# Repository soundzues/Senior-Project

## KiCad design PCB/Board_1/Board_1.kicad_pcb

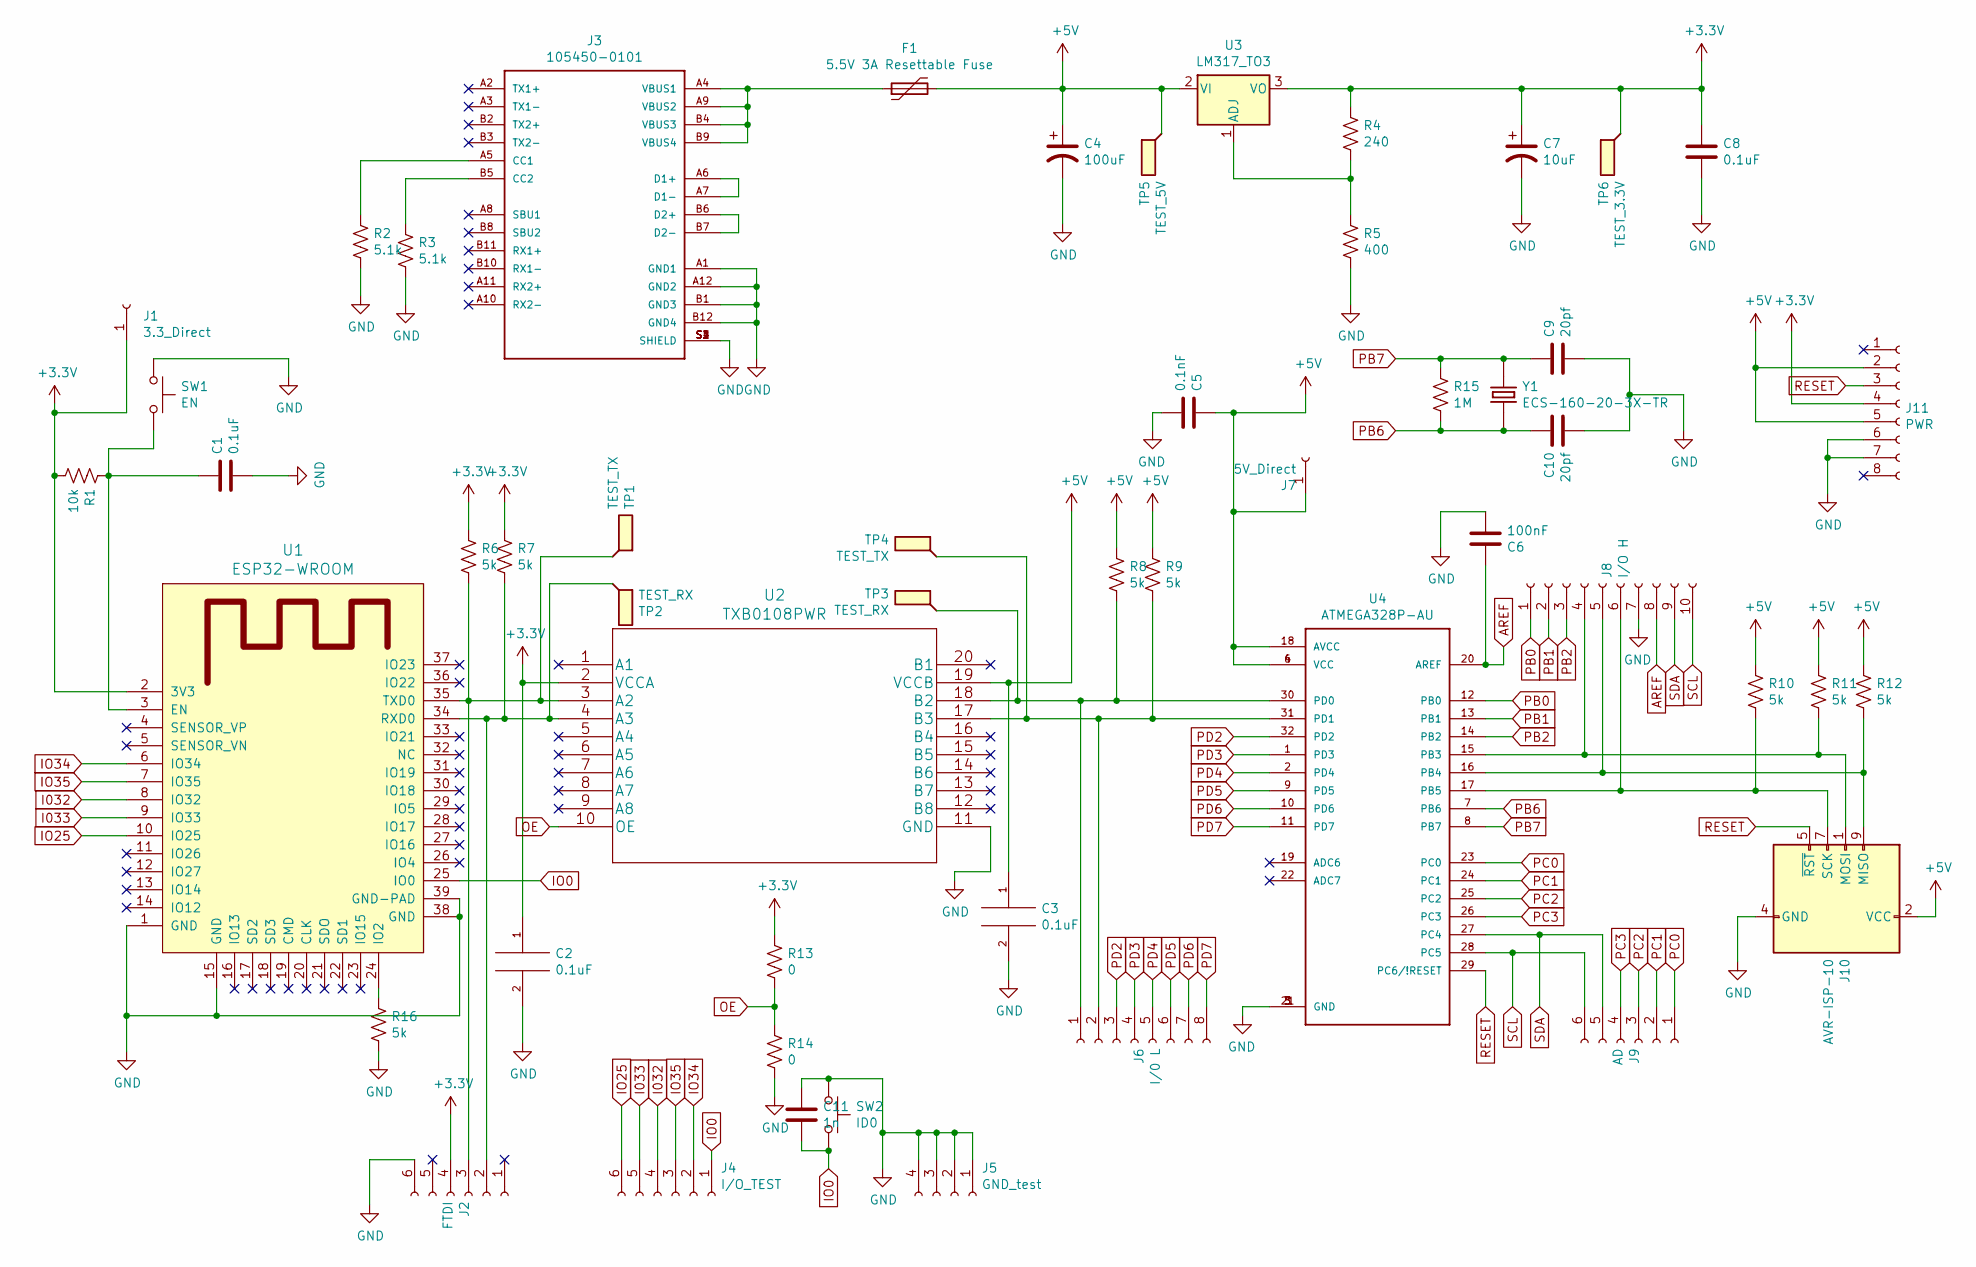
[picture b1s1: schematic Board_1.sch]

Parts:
C1, C2, C3, C8: 0.1uF; C_0603_1608Metric
C4: 100uF; C_0603_1608Metric
C5: 0.1nF; C_0603_1608Metric
C6: 100nF; C_0603_1608Metric
C7: 10uF; C_0603_1608Metric
C9, C10: 20pf; C_0603_1608Metric
C11: 1n; C_0603_1608Metric
F1: 5.5V 3A Resettable Fuse; Fuse_0805_2012Metric
J1: 3.3_Direct; PinHeader_1x01_P2.54mm_Vertical
J2: FTDI; PinHeader_1x06_P2.54mm_Vertical
J3: 105450-0101; MOLEX_105450-0101
J4: I/O_TEST; PinHeader_1x06_P2.54mm_Vertical
J5: GND_test; PinHeader_1x04_P2.54mm_Vertical
J6: I/0 L; PinHeader_1x08_P2.54mm_Vertical
J7: 5V_Direct; PinHeader_1x01_P2.54mm_Vertical
J8: I/O H; PinHeader_1x10_P2.54mm_Vertical
J9: AD; PinHeader_1x06_P2.54mm_Vertical
J10: AVR-ISP-10; PinHeader_2x05_P2.54mm_Vertical
J11: PWR; PinHeader_1x08_P2.54mm_Vertical
R1: 10k; R_0603_1608Metric
R2, R3: 5.1k; R_0603_1608Metric
R4: 240; R_0603_1608Metric
R5: 400; R_0603_1608Metric
R6, R7, R8, R9, R10, R11, R12, R16: 5k; R_0603_1608Metric
R13, R14: 0; R_0603_1608Metric
R15: 1M; R_0603_1608Metric
SW1: EN; SW_PUSH_6mm
SW2: ID0; SW_PUSH_6mm
TP1, TP4: TEST_TX; PinHeader_1x01_P2.54mm_Vertical
TP2, TP3: TEST_RX; PinHeader_1x01_P2.54mm_Vertical
TP5: TEST_5V; PinHeader_1x01_P2.54mm_Vertical
TP6: TEST_3.3V; PinHeader_1x01_P2.54mm_Vertical
U1: ESP32-WROOM
U2: TXB0108PWR
U3: LM317_TO3; TO-220-3_Vertical
U4: ATMEGA328P-AU; QFP80P900X900X120-32N
Y1: ECS-160-20-3X-TR; XTAL_ECS-160-20-3X-TR

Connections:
+3V3: C2.1, C7.1, C8.1, J1.1, J2.4, J11.4, R1.2, R4.1, R6.1, R7.1, R13.1, TP6.1, U1.2 (3V3), U2.2 (VCCA), U3.3 (VO)
+5V: C3.1, C4.1, C5.1, F1.2, J7.1, J10.2 (VCC), J11.2, J11.5, R8.1, R9.1, R10.1, R11.1, R12.1, TP5.1, U2.19 (VCCB), U3.2 (VI), U4.4 (VCC), U4.6 (VCC), U4.18 (AVCC)
AREF: C6.1, J8.8, U4.20 (AREF)
GND: C1.2, C2.2, C3.2, C4.2, C5.2, C6.2, C7.2, C8.2, C9.2, C10.2, C11.1, J2.6, J3.A1 (GND1), J3.A12 (GND2), J3.B1 (GND3), J3.B12 (GND4), J3.S1 (SHIELD), J3.S2 (SHIELD), J3.S3 (SHIELD), J3.S4 (SHIELD), J5.1, J5.2, J5.3, J5.4, J8.7, J10.4 (GND), J10.6 (GND), J10.8 (GND), J10.10 (GND), J11.6, J11.7, R2.2, R3.2, R5.2, R14.2, R16.2, SW1.1, SW2.1, U1.1 (GND), U1.15 (GND), U1.38 (GND), U1.39 (GND-PAD), U2.11 (GND), U4.3 (GND), U4.5 (GND), U4.21 (GND)
I032: J4.4, U1.8 (IO32)
I033: J4.5, U1.9 (IO33)
IO0: C11.2, J4.1, SW2.2, U1.25 (IO0)
IO25: J4.6, U1.10 (IO25)
IO34: J4.2, U1.6 (IO34)
IO35: J4.3, U1.7 (IO35)
unnamed: C1.1, R1.1, SW1.2, U1.3 (EN)
unnamed: F1.1, J3.A4 (VBUS1), J3.A9 (VBUS2), J3.B4 (VBUS3), J3.B9 (VBUS4)
unnamed: J2.2, R7.2, TP2.1, U1.34 (RXD0), U2.4 (A3)
unnamed: J2.3, R6.2, TP1.1, U1.35 (TXD0), U2.3 (A2)
unnamed: J3.A5 (CC1), R2.1
unnamed: J3.A6 (D1+), J3.A7 (D1-)
unnamed: J3.B5 (CC2), R3.1
unnamed: J3.B6 (D2+), J3.B7 (D2-)
unnamed: J6.1, R8.2, TP3.1, U2.18 (B2), U4.30 (PD0)
unnamed: J6.2, R9.2, TP4.1, U2.17 (B3), U4.31 (PD1)
unnamed: J8.4, J10.1 (MOSI), R11.2, U4.15 (PB3)
unnamed: J8.6, J10.7 (SCK), R10.2, U4.17 (PB5)
unnamed: J8.5, J10.9 (MISO), R12.2, U4.16 (PB4)
unnamed: R4.2, R5.1, U3.1 (ADJ)
unnamed: R16.1, U1.24 (IO2)
OE: R13.2, R14.1, U2.10 (OE)
PB0: J8.1, U4.12 (PB0)
PB1: J8.2, U4.13 (PB1)
PB2: J8.3, U4.14 (PB2)
PB6: C10.1, R15.2, U4.7 (PB6), Y1.2
PB7: C9.1, R15.1, U4.8 (PB7), Y1.1
PC0: J9.1, U4.23 (PC0)
PC1: J9.2, U4.24 (PC1)
PC2: J9.3, U4.25 (PC2)
PC3: J9.4, U4.26 (PC3)
PD2: J6.3, U4.32 (PD2)
PD3: J6.4, U4.1 (PD3)
PD4: J6.5, U4.2 (PD4)
PD5: J6.6, U4.9 (PD5)
PD6: J6.7, U4.10 (PD6)
PD7: J6.8, U4.11 (PD7)
RESET: J10.5 (~RST), J11.3, U4.29 (PC6/!RESET)
SCL: J8.10, J9.6, U4.28 (PC5)
SDA: J8.9, J9.5, U4.27 (PC4)

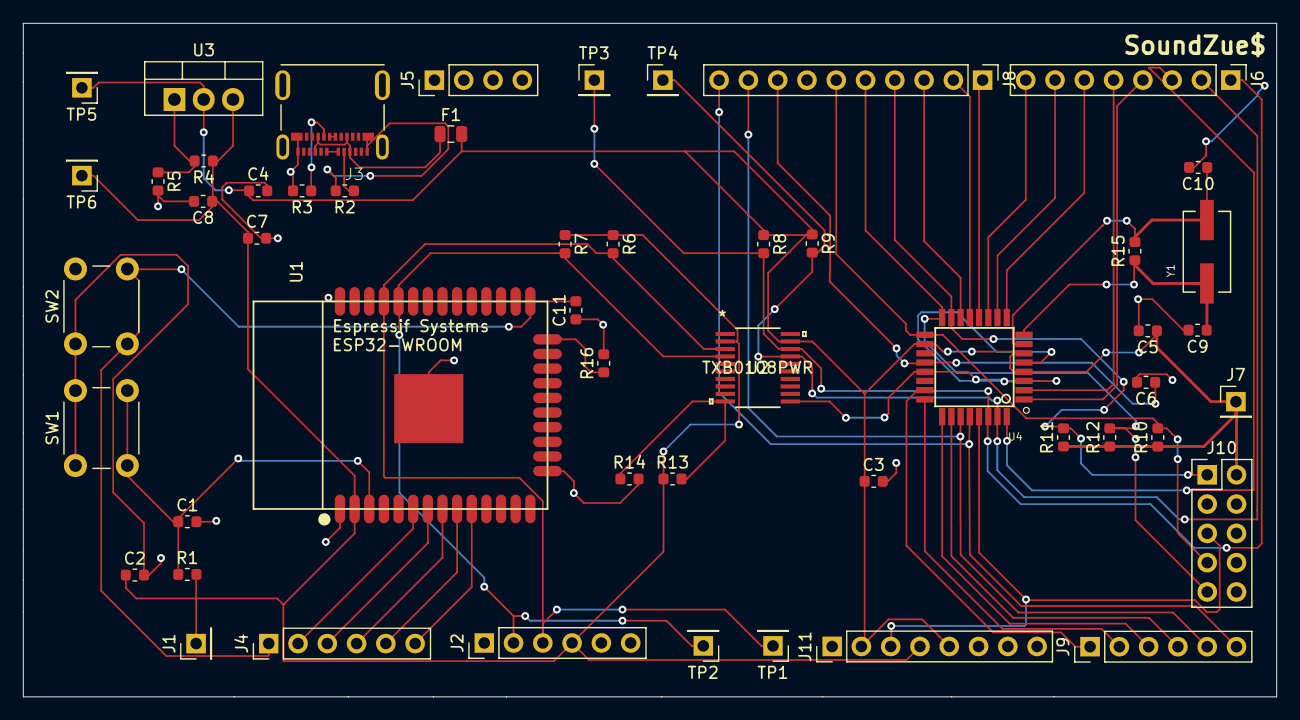
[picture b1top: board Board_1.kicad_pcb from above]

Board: 2 copper layers, 108.7 x 58.4 mm, 52 parts (0 on the bottom side), 44 nets.

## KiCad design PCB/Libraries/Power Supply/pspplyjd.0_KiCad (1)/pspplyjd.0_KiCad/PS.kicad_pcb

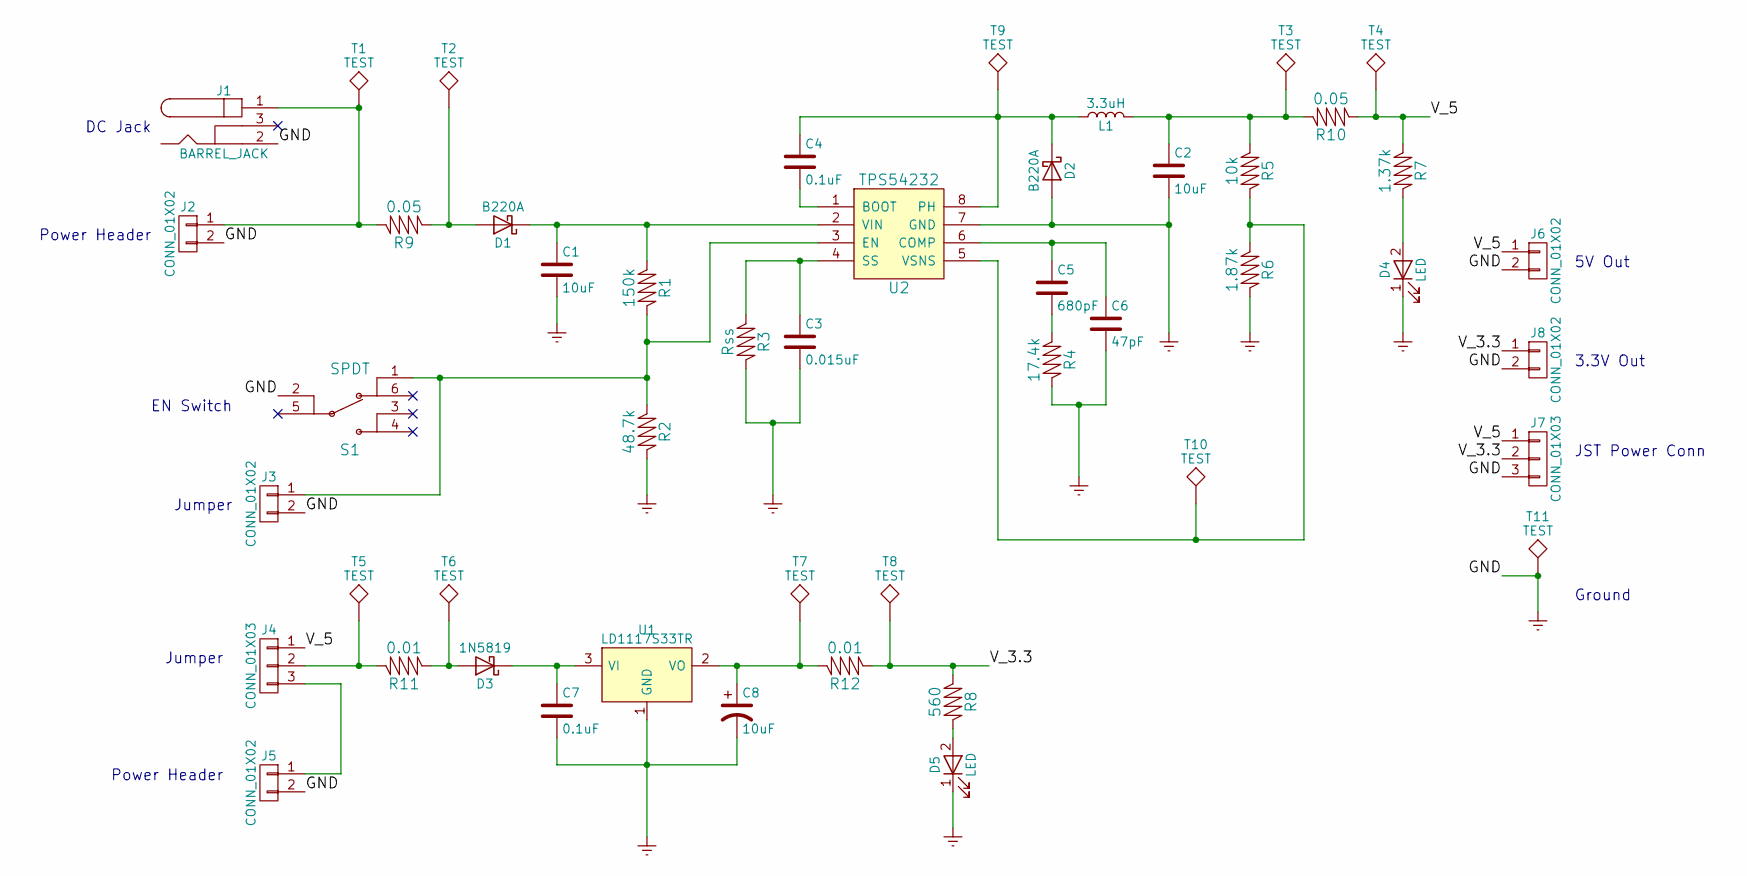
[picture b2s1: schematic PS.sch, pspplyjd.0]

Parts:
C1: 10uF; C_1206_HandSoldering; MPN EEE-1VA100WR; DigiKey PCE3948CT-ND
C2: 10uF; C_1206_HandSoldering; MPN EEE-FK1A220R; DigiKey PCE3774CT-ND
C3: 0.015uF; C_0603_HandSoldering; MPN CC0603KRX7R9BB153; DigiKey 311-1430-1-ND
C4, C7: 0.1uF; C_0603_HandSoldering; MPN CC0603ZRY5V9BB104; DigiKey 311-1343-1-ND
C5: 680pF; C_0603_HandSoldering; MPN CC0603JRNPO9BN681; DigiKey 311-1425-1-ND
C6: 47pF; C_0603_HandSoldering; MPN CC0603JRNPO9BN470; DigiKey 311-1065-1-ND
C8: 10uF; CP_Elec_D4.0mm; MPN EEE-1VA100WR; DigiKey PCE3948CT-ND
D1, D2: B220A; D_SMA; MPN B220A-13-F; DigiKey B220A-FDICT-ND
D3: 1N5819; D_SOD-123; MPN 1N5819HW-7-F; DigiKey 1N5819HW-FDICT-ND
D4, D5: LED; LED_0603_HandSoldering; MPN SML-D12V1WT86; DigiKey SML-D12V1WT86CT-ND
J1: BARREL_JACK; MPN PJ-002A; DigiKey CP-002A-ND
J2, J3, J5, J6, J8: CONN_01X02; Pin_Header_Straight_1x02_Pitch2.54mm; MPN M20-9990246; DigiKey 952-2262-ND
J4: CONN_01X03; Pin_Header_Straight_1x03_Pitch2.54mm; MPN 61300311121; DigiKey 732-5316-ND
J7: CONN_01X03; JST_PH_B3B-PH-K_03x2.00mm_Straight; MPN B3B-EH-A(LF)(SN); DigiKey 455-1612-ND
L1: 3.3uH; L_Sumida_4.9x4.9mm_diag; MPN CDRH4D28CLDNP-3R3PC; DigiKey 308-2037-1-ND
R1: 150k; R_0603_HandSoldering; MPN ERJ-3GEYJ154V; DigiKey P150KGCT-ND
R2: 48.7k; R_0603_HandSoldering; MPN ERJ-3EKF4872V; DigiKey P48.7KHCT-ND
R3: Rss; R_0603_HandSoldering
R4: 17.4k; R_0603_HandSoldering; MPN ERJ-3EKF1742V; DigiKey P17.4KHCT-ND
R5: 10k; R_0603_HandSoldering; MPN RC0603JR-0710KL; DigiKey 311-10KGRCT-ND
R6: 1.87k; R_0603_HandSoldering; MPN ERJ-3EKF1871V; DigiKey P1.87KHCT-ND
R7: 1.37k; R_0603_HandSoldering; MPN ERJ-3EKF1371V; DigiKey P1.37KHCT-ND
R8: 560; R_0603_HandSoldering; MPN ERJ-3GEYJ561V; DigiKey P560GCT-ND
R9, R10: 0.05; R_0603_HandSoldering; MPN ERJ-3BWFR050V; DigiKey P17472CT-ND
R11, R12: 0.01; R_0603_HandSoldering; MPN RUK1608JR010CS; DigiKey 1276-6163-1-ND
S1: SPDT; SPDT_MHSS1104; MPN MHSS1104; DigiKey 679-1848-ND
T1, T2, T3, T4, T5, T6, T7, T8, T9, T10, T11: TEST; TESTPIN
U1: LD1117S33TR; SOT-223; MPN LD1117S33TR; DigiKey 497-1242-1-ND
U2: TPS54232; SOIC-8-N; MPN TPS54232DR; DigiKey 296-39414-1-ND

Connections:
/V_3.3: J7.2, J8.1, R8.2, R12.2, T8.1
/V_5: J4.1, J6.1, J7.1, R7.2, R10.2, T4.1
GNDREF: C1.2, C2.2, C3.2, C6.2, C7.2, C8.2, D2.2 (A), D4.1 (K), D5.1 (K), J1.2, J2.2, J3.2, J5.2, J6.2, J7.3, J8.2, R2.1, R3.1, R4.1, R6.1, S1.2, T11.1, U1.1 (GND), U2.7 (GND)
unnamed: C1.1, D1.1 (K), R1.2, U2.2 (VIN)
unnamed: C2.1, L1.2, R5.2, R10.1, T3.1
unnamed: C3.1, R3.2, U2.4 (SS)
unnamed: C4.1, D2.1 (K), L1.1, T9.1, U2.8 (PH)
unnamed: C4.2, U2.1 (BOOT)
unnamed: C5.1, C6.1, U2.6 (COMP)
unnamed: C5.2, R4.2
unnamed: C7.1, D3.1 (K), U1.3 (VI)
unnamed: C8.1, R12.1, T7.1, U1.2 (VO)
unnamed: D1.2 (A), R9.2, T2.1
unnamed: D3.2 (A), R11.2, T6.1
unnamed: D4.2 (A), R7.1
unnamed: D5.2 (A), R8.1
unnamed: J1.1, J2.1, R9.1, T1.1
unnamed: J3.1, R1.1, R2.2, S1.1, U2.3 (EN)
unnamed: J4.2, R11.1, T5.1
unnamed: J4.3, J5.1
unnamed: R5.1, R6.2, T10.1, U2.5 (VSNS)

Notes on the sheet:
DC Jack
Power Header
Jumper
5V Out
3.3V Out
JST Power Conn
EN Switch
Ground

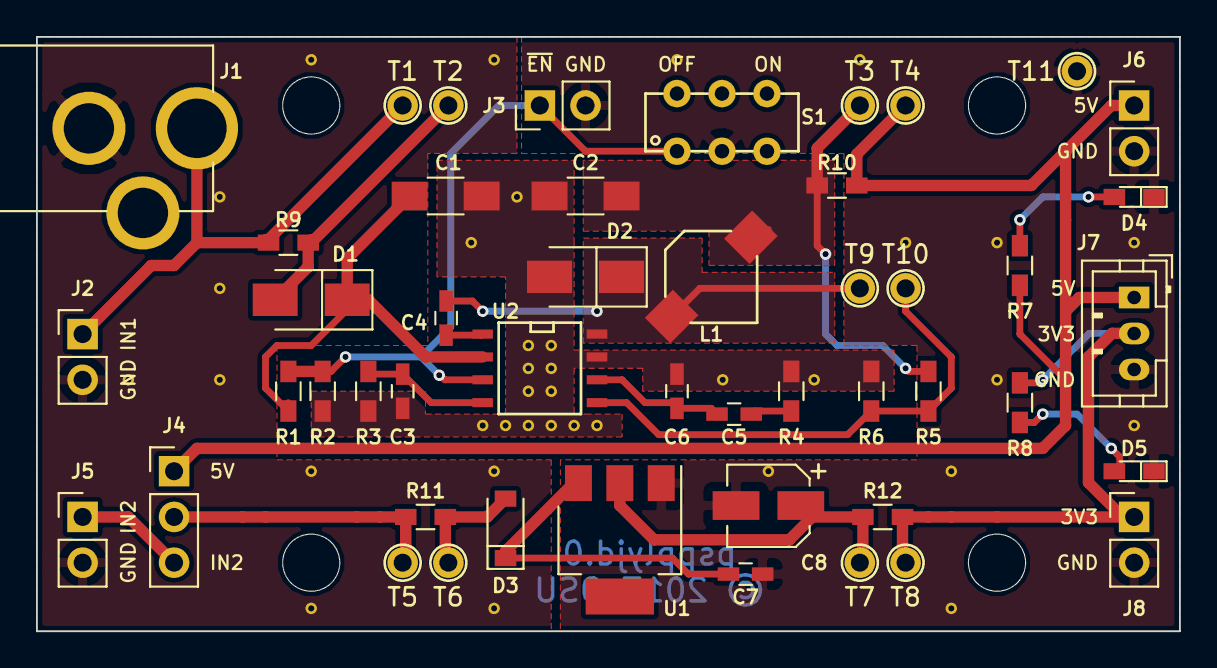
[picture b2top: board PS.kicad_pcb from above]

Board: 2 copper layers, 63.5 x 33.0 mm, 48 parts (0 on the bottom side), 21 nets.

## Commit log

2020-01-15 Touch Screen init
2020-01-15 Touch Screen GUI init
2020-01-15 Created 3 Rectangles for buttons
2020-01-15 Fixed from Portrait to Landscape, added 3 OPTs
2020-01-18 button UI in progress
2020-01-18 Got First button's location right
2020-01-18 3 Button Layout for GUI, Button 3 broken
2020-01-19 Created Custom Buttons, work Perfectly
2020-01-19 3 properly spaced button, white
2020-01-22 Fixed Sending Data to touch Screen, Need to improve
2020-01-23 Bidirectional message, 2 prob: debounce, cursor
2020-02-16 PCB in works
2020-02-16 PCB Schematic & Footprint match Done
2020-02-24 PCB first board ready/Debugging UART

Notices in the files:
PCB/Libraries/Power Supply/pspplyjd.0_KiCad (1)/pspplyjd.0_KiCad/PS.kicad_pcb:
© 2017 OSU
parts and their libraries:
Copyright 2016 Accelerated Designs. All rights reserved.
